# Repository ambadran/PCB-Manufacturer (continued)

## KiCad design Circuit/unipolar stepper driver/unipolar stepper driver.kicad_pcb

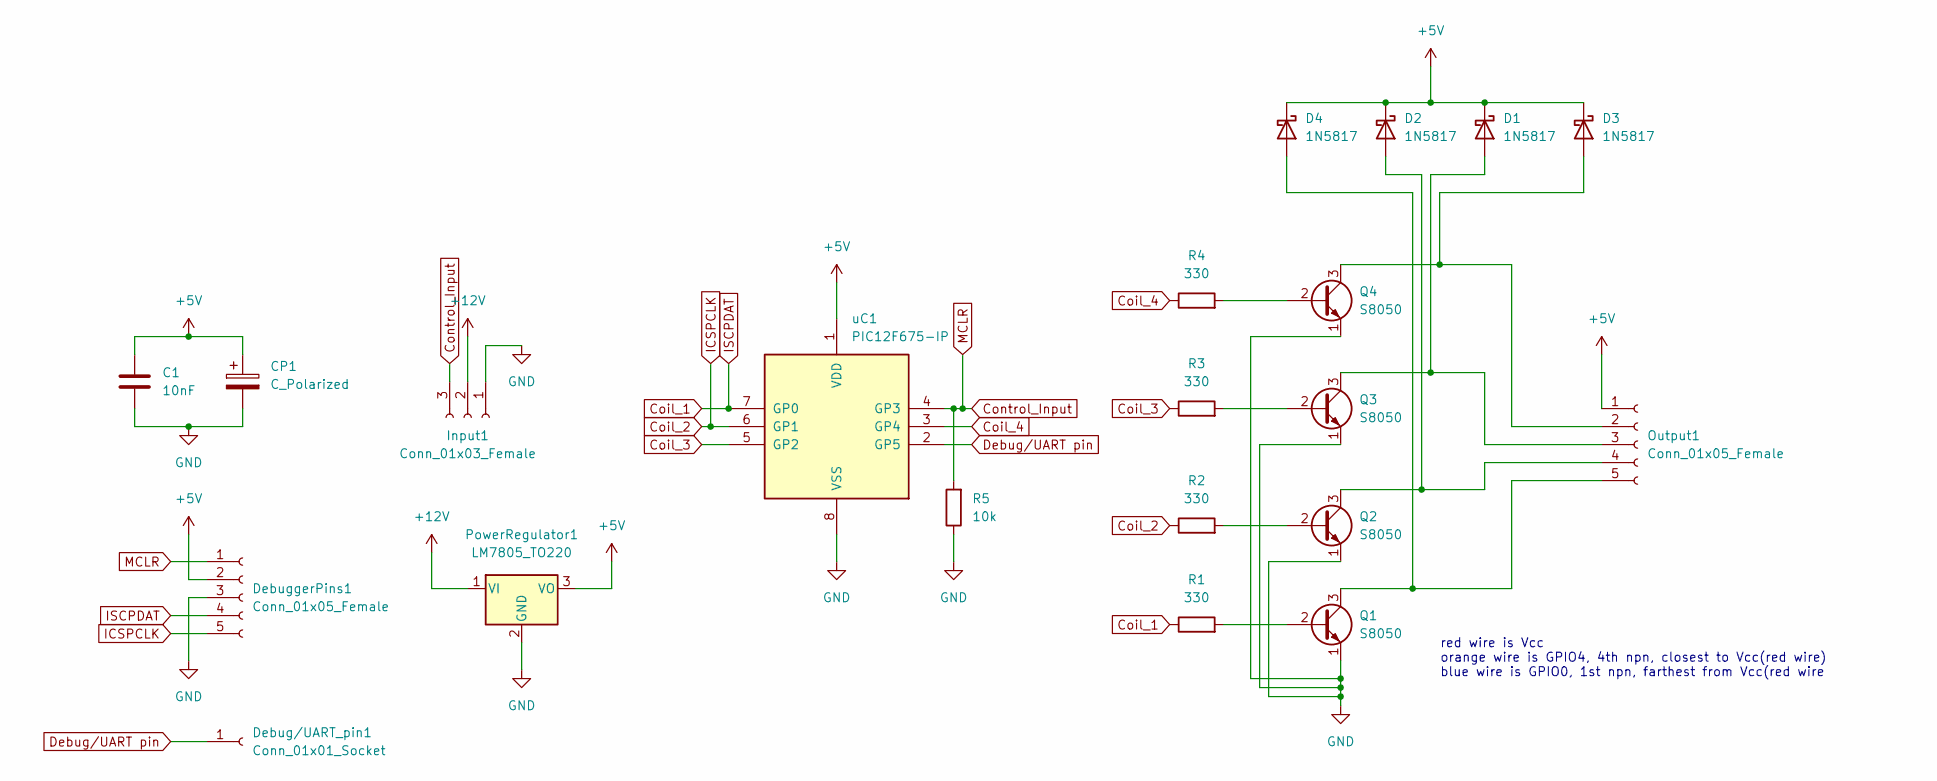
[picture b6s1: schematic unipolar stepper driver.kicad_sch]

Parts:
C1: 10nF; C_Disc_D3.0mm_W2.0mm_P2.50mm
CP1: C_Polarized; CP_Radial_D5.0mm_P2.50mm
D1, D2, D3, D4: 1N5817; D_DO-34_SOD68_P7.62mm_Horizontal
Debug/UART_pin1: Conn_01x01_Socket; PinSocket_1x01_P2.54mm_Vertical
DebuggerPins1: Conn_01x05_Female; PinHeader_1x05_P2.54mm_Vertical
Input1: Conn_01x03_Female; PinHeader_1x03_P2.54mm_Vertical
Output1: Conn_01x05_Female; PinHeader_1x05_P2.54mm_Vertical
PowerRegulator1: LM7805_TO220; TO-220-3_Vertical
Q1, Q2, Q3, Q4: S8050; TO-92_Inline
R1, R2, R3, R4: 330; R_Axial_DIN0207_L6.3mm_D2.5mm_P7.62mm_Horizontal
R5: 10k; R_Axial_DIN0207_L6.3mm_D2.5mm_P7.62mm_Horizontal
uC1: PIC12F675-IP; DIP-8_W7.62mm

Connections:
+5V: C1.2, CP1.1, D1.1 (K), D2.1 (K), D3.1 (K), D4.1 (K), DebuggerPins1.2, Output1.1, PowerRegulator1.3 (VO), uC1.1 (VDD)
+12V: Input1.2, PowerRegulator1.1 (VI)
Coil_1: DebuggerPins1.4, R1.1, uC1.7 (GP0)
Coil_2: DebuggerPins1.5, R2.1, uC1.6 (GP1)
Coil_3: R3.1, uC1.5 (GP2)
Coil_4: R4.1, uC1.3 (GP4)
Control_Input: DebuggerPins1.1, Input1.3, R5.2, uC1.4 (GP3)
Debug/UART pin: Debug/UART_pin1.1, uC1.2 (GP5)
GND: C1.1, CP1.2, DebuggerPins1.3, Input1.1, PowerRegulator1.2 (GND), Q1.1 (E), Q2.1 (E), Q3.1 (E), Q4.1 (E), R5.1, uC1.8 (VSS)
unnamed: D1.2 (A), Output1.3, Q3.3 (C)
unnamed: D2.2 (A), Output1.4, Q2.3 (C)
unnamed: D3.2 (A), Output1.2, Q4.3 (C)
unnamed: D4.2 (A), Output1.5, Q1.3 (C)
unnamed: Q1.2 (B), R1.2
unnamed: Q2.2 (B), R2.2
unnamed: Q3.2 (B), R3.2
unnamed: Q4.2 (B), R4.2

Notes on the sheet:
red wire is Vcc orange wire is GPIO4, 4th npn, closest to Vcc(red wire) blue wire is GPIO0, 1st npn, farthest from Vcc(red wire

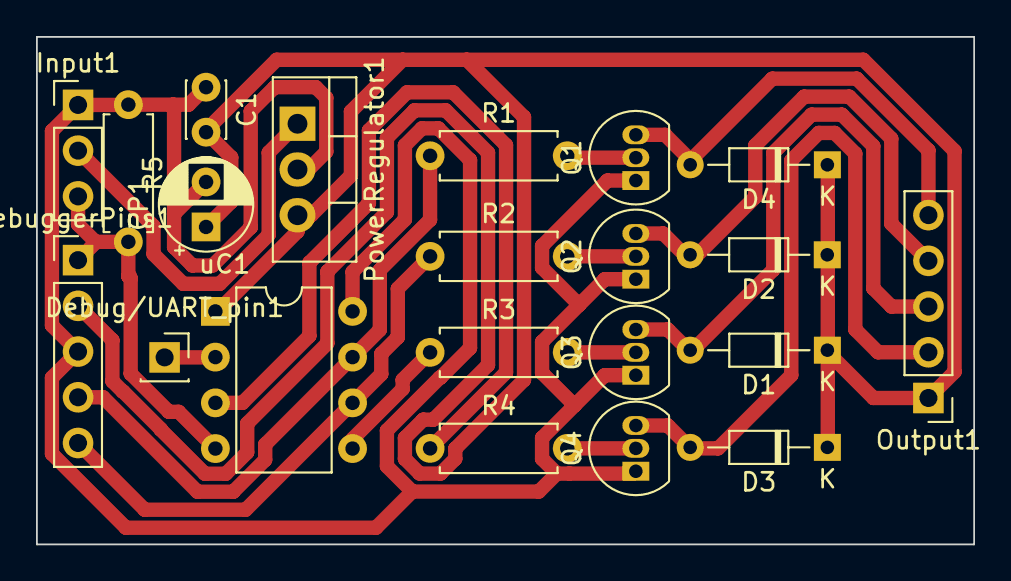
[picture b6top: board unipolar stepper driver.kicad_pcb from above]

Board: 2 copper layers, 52.1 x 28.2 mm, 21 parts (0 on the bottom side), 17 nets.

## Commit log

2022-11-08 Fixed Merge conflict
2022-11-08 Added .gitignore
2022-11-08 Removed .DS_Store
2022-11-13 First Windows Commit
2022-11-17 Removed the stupid .DS_Store
2022-11-20 Added grbl for Arduino Uno files for testing
2022-11-21 Added Arduino grbl pinout
2022-11-22 Renamed and rearranged Programming folders
2022-11-24 Corrected file structure to work with arduino
2022-11-26 Added PyCNC files
2022-11-26 Understanding the grbl code
2022-11-29 29 Nov trying to understand grbl ubuntu
2022-11-30 ADDED LATCH COMMAND to grbl files
2022-12-02 Fixed latch state not saved
2022-12-03 Added power supply enable and tool select gcode commands
2022-12-08 Added esp8266 code
2022-12-09 added raspberry pi pico w files
2022-12-10 Fixed wifi files
2022-12-10 latest Wifi build
2022-12-11 Modified unipolar driver pic code
2022-12-13 Unipolar Driver is now state controlled instead of trigger controlled
2022-12-13 modified .gitignore
2022-12-14 Modified unipolar driver code and PWM multiplexer circuit
2022-12-17 Modified PWM output frequency to 976Hz and range of S value is 0-250
2022-12-18 Modified unipolar driver circuit and generated outputs
2022-12-18 created gerber files for unipolar circuit
2022-12-18 Modified unipolar gerber file
2022-12-25 Added PSU control Circuit
2022-12-25 Added DXF files for PSU controller circuit
2022-12-25 Added Gerber files for PSU controller
2022-12-27 Created GRBL Controller file
2022-12-27 Created Unipolar Stepper PCB design
2022-12-27 Started DC Motor Driver Circuit schematic
2022-12-28 Modified PSU controller circuit
2022-12-30 Finished DC Motor Driver Circuit, Schematic Design, testing and PCB design
2023-01-05 Finished PCB hole CAM module
2023-01-20 Small useless modification to tool_select.c
2023-01-21 started limit switch circuit development
2023-01-31 Developing limit switch circuit
2023-02-15 Fixing the random movement unipolar driver bug
2023-02-16 further attempt at fixing unipolar driver bug
2023-02-19 Finally Fixed Unipolar driver bug
2023-02-21 added new pics for various circuits
2023-02-23 Debugging limit switch high distance travel problem
2023-02-23 further trials to solve limit switch high distance problem
2023-02-23 further debugging of limit switch problem
2023-02-23 Finally understood that i have to change ;)
2023-02-23 Added Description of homing_pull_off problem in limits.c
2023-02-23 Final change in limit switch problem saga
2023-02-27 MinorChanges
2023-03-01 Updated CAM framework to facilitate further development
2023-03-01 further development in CAM module
2023-03-05 Updated .gitignore
2023-03-05 added UGS
2023-03-05 Removed UGS
2023-03-06 Finished developing ink-laying gcode gernator and made progress in creating the tcp-to-uart bridge on esp8266
2023-03-08 Further development in the ESP8266 saga
2023-03-12 Fixed extract block bug and started implementing laser gcode generator
2023-03-15 Further development in CAM module and unipolar code
2023-03-16 Major Code renovation in cam module ->OOP
2023-03-20 Finished gerber_tools.py OOP development
2023-03-20 Integrated new OOP code with 'main.py' and 'gcode_tools.py'
2023-03-20 Fixed Stupid coordinate variable copying bug
2023-03-21 Further development in the laser pcb trace gcode generator algorithm
2023-03-22 Further development in laser cam module
2023-03-24 Almost finished Graph seperation algorithm and started apply_offset algorithm
2023-03-25 Fixed Graph.sererate() and started DP for getting continious round-trip trace track
2023-03-26 Algebraic Equation for applying offset and further development in .order_graph() algorithm
2023-03-26 Further development in .order_graph()
2023-03-27 Further development in Edge.sort_rightmost()
2023-03-28 Further development in Edge.anticlockwise sort and Graph.order
2023-03-29 Finished Edge.clockwise_order() :)
2023-03-29 Completely changed the design and implementaiton of Edge.clockwise_order
2023-03-30 Finished Edge.anticlockwise_successors and graph.ordered_edges :)))
2023-03-31 Further development in Edge.apply_offset()
2023-03-31 Major development in Edge.apply_offset()
2023-04-01 further development in graph.apply_offset
2023-04-02 First no-error run of Edge.apply_offset :) (although bugs available)
2023-04-03 LOTS OF BUG FIXES for Edge.apply_offset()
2023-04-03 Identifying new bugs -> new corner cases in Edge.apply_offset()
2023-04-03 Another huge patch of bug fixes for Edge.apply_offsets(new corner cases)
2023-04-05 Implemented Coordinate.generate_semicircle_coords() except for infinity gradient corner case
2023-04-05 minor changes
2023-04-06 Implemented corner case for m=0 and m=infinity for Coordinate.semicircle_generate_coords()
2023-04-07 further development in Coordinate.generate_semicircle()
2023-04-07 Finished generate_semicircle() and First successful run Graph.apply_offset WITH SEMICIRCLES GENERATEDgit add .
2023-04-08 Fixed missing semicircle coords problem
2023-04-09 Finished remove_v model
2023-04-11 Started implementing remove_vertex() and remove_edge()
2023-04-11 further development in .remove_vertex and .remove _edge
2023-04-12 Finished Implementing Graph.filter_tiny_edges() :)
2023-04-15 Planning for .incorporate_componentpad()
2023-04-16 Started implementing .incorporate_componentpads() and .point_edge_intersection()
2023-04-18 Further development in .point_edge_intersection()
2023-04-18 Further development in .add_comppad()
2023-04-23 some changes
2023-04-25 Finished step1: finding intersections_data in Node.add_comppad()
2023-04-25 designed and developed ShapeType.Rectangle case in .point_edge_intersection()
2023-04-28 Bug fixes for previous commit
2023-04-28 finished step2 delete and add comppad vertices in .add_comppad()
2023-04-29 started modifing .generate_semicircle_coords() to generate arc coords
2023-04-29 Further dev
2023-05-02 Further fixing in the stupid corner cases' corner cases ;)
2023-05-05 Finished intersection detecting algorithm ;) now working on linkedlist node replacing algorithm
2023-05-07 Hopefully in the final stages in perfecting the .add_comppad() two algorithms ;)
2023-05-07 furhter dev
2023-05-09 I think I finished the main algorithm to add component pads to offseted lines ;|
2023-05-10 .add_comppad() works on default.gbr not test2.gbr
2023-05-24 developing a terminal tool
2023-05-25 Finished generate_circle_coords and developed in generate_rec_coords for comppads
2023-05-25 finished implementing the rectangle comppad coords generator
2023-05-28 Further development in comppad_generator()
2023-05-30 Furhter dev in rec_comppad()
2023-05-30 Should be finishing soon witht he rec_comppad_coords()
2023-05-31 further dev in generate_comppad_nodes
2023-06-02 new architecture for rec_comppad() for the millionth time
2023-06-03 Created an algorithm that creates proper gcode for default.gbr (except Oval comppads are treated as Rectangle Comppads)
2023-06-08 bug fixes
2023-06-08 Bug Fixes after gerber.mirror() implementation
2023-06-08 CLI bug fix and --laser-debug implemented
2023-06-08 boolean CLI arguments don't need True, they work like normal cli commands now
2023-06-08 CNC Tuning
2023-06-16 Fixing the unipolar driver bug
2023-06-16 Further dev in unipolar driver
2023-06-21 Finally found a way to implement FULL software uart on pic12f675
2023-06-22 more dev in unipolar
2023-06-23 Finally implemented non-constant CW_CCW steps
2023-07-11 all files updated after OS change for some reason
2023-07-15 created new gcode file for PSU circuit
2023-07-15 new PSU gcode
2023-07-26 Started new project PCB clamping system
2023-07-31 Fixed numerous bugs in CAM module and marked numerous others
2023-08-02 Further bug fixing for unipolar_driver.gbr CAM module
2023-08-04 one bug remaining for unipolar_driver.gbr cam module test case
2023-08-04 Bug fix finished for unipolar_driver.gbr :)
2023-08-05 Added multi-pass, include_edge_cuts and other cam Module tiny features
2023-10-18 unipolar circuit development
2023-10-30 Finished PWM Multiplexer circuit schematics and started PCB design
2023-10-31 Fixed diode directions in unipolar_driver circuit
2023-10-31 Added different Z feedrates for drill down operation and up from pcb
2023-10-31 PWM multiplexer circuit PCB traces ALL connected in a preliminary manner
2023-11-01 Further development in PWM Multiplexer circuit PCB final design
2023-11-11 looks like CAM module needs bug fixing again
2023-11-19 Finished limit switch circuit and minor changes to cam module
2023-11-19 Fixed DC Motor Circuit and discovered fatal design flaw in PWM demultiplexer
2023-11-22 Started developing for Oval component pads
2023-11-26 redesigning PWM Multiplexer PCB Solution
2023-11-27 Further development in PWM Multiplexer PCB solution
2023-11-29 added passive filters to limit switch circuit
2023-12-13 Implemented Isolators in PWM Mutliplexer
2023-12-13 added optical isolation to PWM demultiplexer circuit schematic
2024-01-10 finished PWM multiplexer circuit final version
2024-01-10 DC Motor Driver Circuit fine tuning for manufacturing
2024-01-20 started developing esp32-cam software
2024-01-22 figured out full control of esp32-cam through micropython
2024-02-16 further development in esp32-cam
2024-02-26 Added some gerber files and gcode files for some of the circuit pcbs
2024-06-03 removed .ca folder
2024-06-03 removed gcode files
2024-09-24 added .step file and some media
2024-09-24 cleaned Programming file
2024-09-24 modified README file
